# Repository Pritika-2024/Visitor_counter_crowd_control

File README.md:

# Secure Visitor Counter with Crowd Control

> An automated visitor monitoring and crowd control system using IR sensors, servo motor, 16x2 LCD and a 4x4 keypad — built on Arduino Uno. The system restricts entry once maximum occupancy is reached and allows access only through registration number verification.

---

## Table of Contents
- How It Works
- Circuit
- Hardware Implementation
- PCB Design
- Components
- Libraries Used
- Source Code
- Results

---

## ⚙️ How It Works

The system uses two IR sensors — one at the entry and one at the exit — to detect movement and maintain an accurate real-time visitor count. The Arduino Uno processes all sensor signals, manages the door mechanism, and enforces the maximum occupancy limit.
<p align="center">
<b> Block Diagram </b>

</p>

**Step-by-step flow:**

**1. System Initialization** — On power-up, the Arduino initializes all peripherals. The LCD displays `Visitor Counter | Count: 0/4` and the servo motor holds the door in the closed position.

**2. Entry Detection** — When the IR entry sensor detects a person (output goes LOW), the system checks if the current count is below the maximum limit (4). If within limit, it prompts `Enter Reg. Number` on the LCD.

**3. Registration Verification** — The user enters a 4-digit number via the 4x4 keypad. The Arduino compares this against a stored list of valid registration numbers. If valid, the count increments and the door opens. If invalid, `Invalid Number` is shown and entry is denied.

**4. Door Control** — On successful verification, the servo motor rotates to 90° (door open), holds for 3 seconds, then returns to 0° (door closed). A `doorMoving` flag prevents any new sensor triggers during this operation.

**5. Exit Detection** — When the IR exit sensor detects a person leaving, the count decrements automatically. No verification is needed for exit. A debounce delay of 1000ms prevents false triggers.

**6. Crowd Control Enforcement** — If `visitor_count == maxVisitors`, the system sets `maxCountReached = true` and displays `Max Count Reached | Entry Prohibited`. The door will not open for new entries until the count drops below the limit.

**7. Continuous Monitoring** — The main loop continuously polls both sensors in real time, handling all entry and exit events without any manual intervention.

---

##  Circuit

The Arduino Uno is the central controller. Both IR sensors connect to digital input pins D2 and D3. The servo motor PWM signal goes to D9. The LCD communicates over I2C using A4 (SDA) and A5 (SCL), which reduces wiring to just 4 wires. The 4x4 keypad uses 8 digital pins — rows on D4, D5, D6, D7 and columns on D8, D10, D11, D12.
<p align="center">
<b> Circuit Diagram </b>

</p>

| Component | Arduino Pin |
|---|---|
| IR Entry Sensor (OUT) | D2 |
| IR Exit Sensor (OUT) | D3 |
| Servo Motor (Signal) | D9 |
| LCD SDA | A4 |
| LCD SCL | A5 |
| Keypad Rows | D4, D5, D6, D7 |
| Keypad Columns | D8, D10, D11, D12 |

---

## Hardware Implementation

The system was physically assembled and tested using a cardboard door model named "Mondini Hall." The LCD and keypad were mounted on the front panel for user interaction. The Arduino, servo, and IR sensors were wired behind the frame. The servo arm was mechanically linked to a door flap to simulate real door open/close operation.

<p align="center">
<b> Hardware Implementation </b>

</p>
---

##  PCB Design

The schematic and PCB were designed in KiCad to convert the breadboard prototype into a production-ready layout. The schematic captures all component connections and net assignments. The PCB consolidates these into a compact single-layer board with clearly labeled pads for each peripheral.
<p align="center">
<b> Schematic Diagram </b>

</p>

<p align="center">
<b> PCB layout </b>

</p>

The 3D view confirms component placement and checks for mechanical clearance before fabrication.
<p align="center">
<b> 3D view </b>

</p>
---

##  Components

| # | Component | Qty | Cost |
|---|---|---|---|
| 1 | Arduino Uno (ATmega328P) | 1 | ₹230 |
| 2 | 16x2 LCD Display with I2C module | 1 | ₹150 |
| 3 | IR Obstacle Sensor (2–30cm range) | 2 | ₹80 |
| 4 | Micro Servo Motor SG90 | 1 | ₹40 |
| 5 | 4x4 Matrix Membrane Keypad | 1 | ₹100 |
| | **Total** | | **₹600** |

---

##  Libraries Used

| Library | Purpose |
|---|---|
| `LiquidCrystal_I2C` | Controls the 16x2 LCD over I2C protocol. Uses only 2 wires (SDA, SCL) instead of the standard 6–8 pin parallel interface, simplifying wiring significantly. |
| `Wire` | Provides I2C communication support for Arduino. Required as a dependency by `LiquidCrystal_I2C` to handle the low-level data transmission between Arduino and the LCD module. |
| `Servo` | Manages PWM signal generation for the SG90 servo motor. Allows precise angle control (0°–180°) using simple `servo.write(angle)` commands without manually handling PWM timing. |
| `Keypad` | Handles 4x4 matrix keypad scanning using row-column multiplexing. Detects key presses by sequentially pulling rows low and reading column states, reducing 16 buttons to just 8 pins. |

**Install via Arduino IDE:**
`Sketch → Include Library → Manage Libraries → Search each library name`

---

##  Source Code

| File | Description |
|---|---|
| [`src/Code.cpp`](./01_Visitor_counter_using_ArduinoUNO/01_src/Code.cpp) | Main Arduino source code — visitor counting logic |
| [`02_Visitor_simulation/sketch.ino`](./01_Visitor_counter_using_ArduinoUNO/02_Visitor_simulation/sketch.ino) | Wokwi online simulation sketch |
| [`02_Visitor_simulation/diagram.json`](./01_Visitor_counter_using_ArduinoUNO/02_Visitor_simulation/diagram.json) | Wokwi circuit wiring diagram |
| [`02_Visitor_simulation/libraries.txt`](./01_Visitor_counter_using_ArduinoUNO/02_Visitor_simulation/libraries.txt) | Library dependencies for simulation |
| [`03_PCB/Schematic.kicad_sch`](./01_Visitor_counter_using_ArduinoUNO/03_PCB/Schematic.kicad_sch) | KiCad schematic source file |
| [`03_PCB/PCB_design.kicad_pcb`](./01_Visitor_counter_using_ArduinoUNO/03_PCB/PCB_design.kicad_pcb) | KiCad PCB layout source file | | [`03_PCB/Visitor_Counter.kicad_pro`](./01_Visitor_counter_using_ArduinoUNO/03_PCB/Visitor_Counter.kicad_pro) | KiCad project file |

**Default valid registration numbers:**
```
1238 | 5678 | 9101 | 1121
```
> To modify, update the `validRegistrationNumbers[]` array in [`01_src/03_a.cpp`](01_src/03_a.cpp)

---

## Results

The system was tested across multiple scenarios and performed accurately in all cases.

When the system powers on, the LCD initializes with `Visitor Counter | Count: 0/4`. Upon entry detection, the system successfully prompts for a registration number. Entering a valid number increments the count, opens the servo door for 3 seconds, and updates the display. An invalid number shows `Invalid Number` for 2 seconds before returning to idle.

The exit sensor correctly decrements the count each time a person leaves, and the `maxCountReached` flag resets automatically, re-enabling entry. When all 4 slots are occupied, the LCD switches to `Max Count Reached | Entry Prohibited` and the door remains locked regardless of sensor triggers.

The debounce mechanism successfully prevented false triggers on both entry and exit sensors during rapid movement testing.

| Test Case | Input | Result |
|---|---|---|
| Power ON | — | `Visitor Counter / Count: 0/4`  |
| Valid entry | Reg. No: 1238 | Count increments, door opens |
| Invalid entry | Reg. No: 0000 | `Invalid Number` shown  |
| Max capacity | Count = 4 | `Max Count Reached / Entry Prohibited`  |
| Exit detected | IR Exit triggered | Count decrements, entry re-enabled  |
| Incomplete input | Less than 4 digits + # | `Enter 4 digits!` shown |

---

##  License

This project is licensed under the [MIT License](LICENSE).

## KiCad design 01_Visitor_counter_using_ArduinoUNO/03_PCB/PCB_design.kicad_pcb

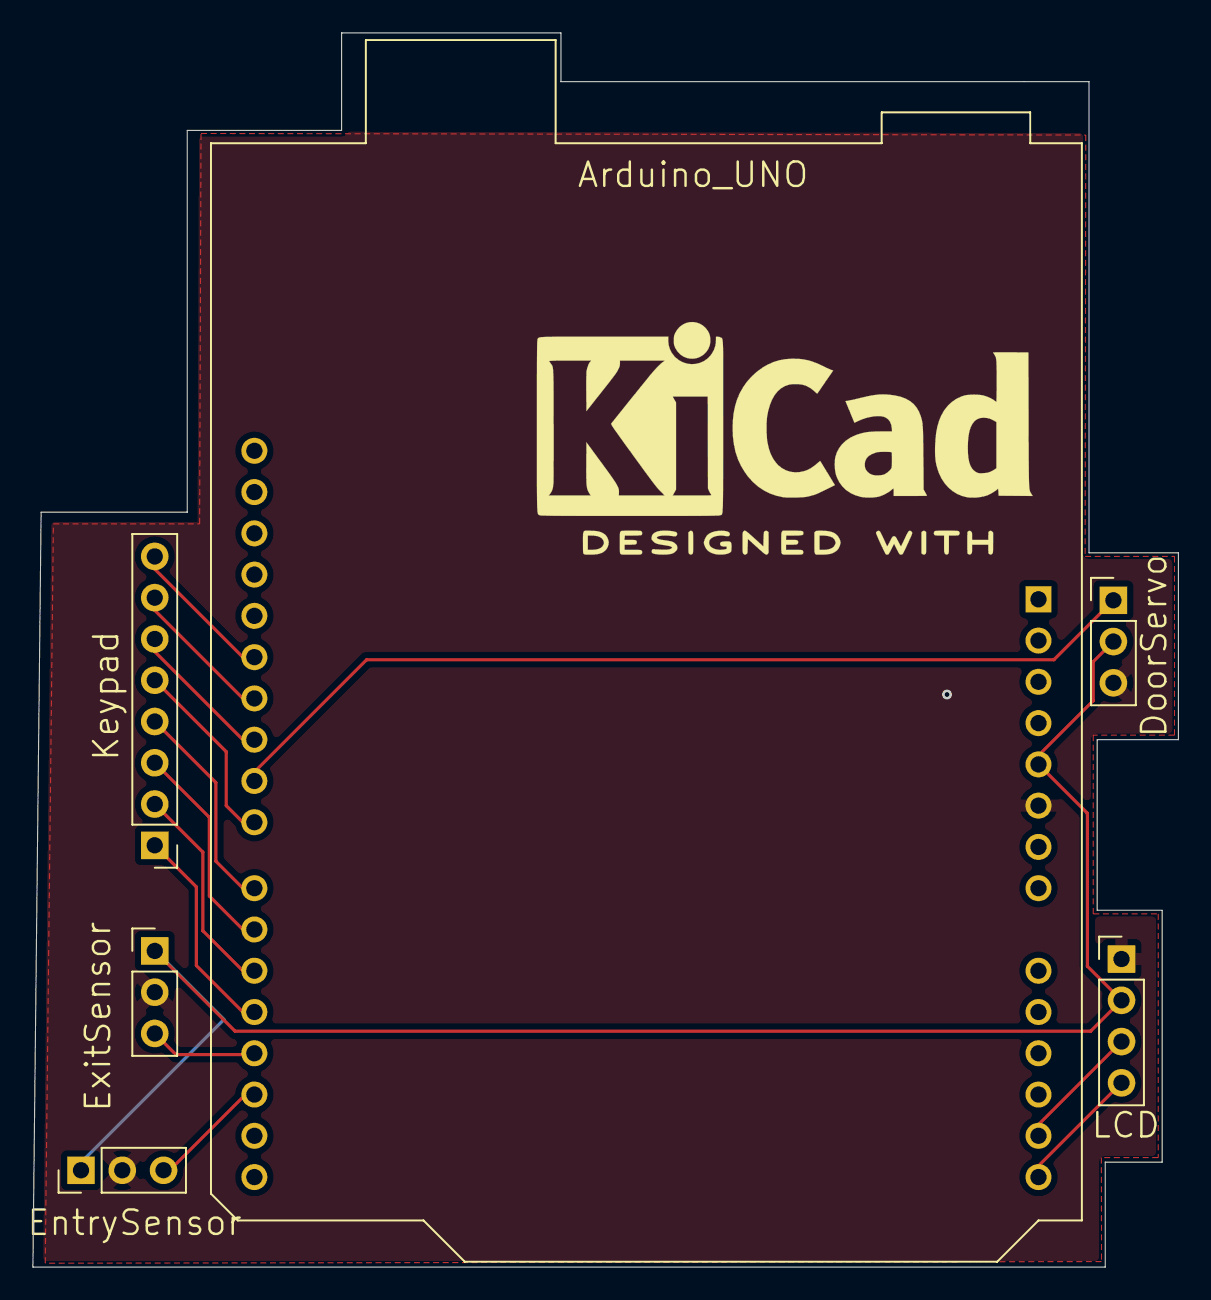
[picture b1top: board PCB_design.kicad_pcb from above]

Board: 2 copper layers, 70.5 x 76.0 mm, 6 parts (0 on the bottom side), 15 nets.

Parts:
Arduino_UNO: Arduino; Arduino_UNO_R3
DoorServo: PinHeader_1x03_P2.54mm_Vertical
EntrySensor: PinHeader_1x03_P2.54mm_Vertical
ExitSensor: PinHeader_1x03_P2.54mm_Vertical
Keypad: 4x4; PinHeader_1x08_P2.54mm_Vertical
LCD: PinHeader_1x04_P2.54mm_Vertical

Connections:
GND: Arduino_UNO.6 (GND), DoorServo.3 (-), EntrySensor.2, ExitSensor.2, LCD.1
unnamed: Arduino_UNO.5 (+5V), DoorServo.2 (+), EntrySensor.1, ExitSensor.1, LCD.2
unnamed: Arduino_UNO.17 (D2), EntrySensor.3
unnamed: Arduino_UNO.18 (D3), ExitSensor.3
unnamed: Arduino_UNO.19 (D4), Keypad.1
unnamed: Arduino_UNO.20 (D5), Keypad.2
unnamed: Arduino_UNO.21 (D6), Keypad.3
unnamed: Arduino_UNO.22 (D7), Keypad.4
unnamed: Arduino_UNO.23 (D8), Keypad.5
unnamed: Arduino_UNO.24 (D9), DoorServo.1 (PWM)
unnamed: Arduino_UNO.25 (D10), Keypad.6
unnamed: Arduino_UNO.26 (D11), Keypad.7
unnamed: Arduino_UNO.27 (D12), Keypad.8
unnamed: Arduino_UNO.13 (SDA/A4), LCD.3
unnamed: Arduino_UNO.14 (SCL/A5), LCD.4

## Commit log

2026-03-31 Rename repository and enhance README description
    Updated project name and formatted description.
2026-03-31 Enhance README with project title and description
    Updated project title formatting and added description.
2026-03-31 Images update
2026-03-31 report
2026-03-31 readme
2026-03-31 Revise README with updated images and description
    Updated image links and improved project description.
2026-03-31 Fix block diagram image path in README
    Corrected the file path for the block diagram image in the README.
2026-03-31 Fix image display for block diagram in README
    Updated image syntax for block diagram in README.
2026-03-31 Fix image tags in README.md
    Updated image syntax in README for better compatibility.
2026-03-31 Modify image tags and heights in README.md
    Updated image tags in README.md to use local paths and adjusted heights for better display.
2026-03-31 Enhance README formatting and add block diagrams
    Updated README to improve formatting and add images.
2026-03-31 Update README with circuit and component details
2026-03-31 Rearrange pin assignments and key mapping
